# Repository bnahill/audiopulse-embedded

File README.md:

Android HiFi DPOAE Audio Interface
===================

This is part of the [Sana AudioPulse project](http://sana.mit.edu/audiopulse/) and may someday be officially moved over there.

The basic objective is an audio interface for an Android phone to output high-fidelity audio (two channels) to an earpiece and to record back audio from a microphone in the earpiece. As the features-of-interest in the response are below 0dB SPL, this requires very high precision.

Licensing
===================
This is an open-source project. Except where otherwise stated, this work is copyright 2014, Ben Nahill, free to be used, modified, and redistributed in accordance with terms of the GPLv3 license. Note that initially it was provided under a BSD-3 license.

Components
===================

*Updated to refer to rev2*

Control
-------------------
The main controller onboard is a Freescale Kinetis K20 ARM Cortex-M4 microcontroller. It has a 72MHz DSC core (running at 48MHz), a USB OTG interface with full-speed PHY, a full-duplex I2S interface to communicate with the CODEC, I2C to communicate with the headphone amplifier.

The USB interface is capable of up to 12Mb/s, which should support full-duplex 24-bit audio at 48kHz, which should require ~4.4Mb/s plus some inefficiency. That's fine but Android doesn't yet support USB audio input so processing is done onboard. An efficient mixed-precision C++ DSP library is included to perform processing similiar to that described in James Hall's *Handbook of Otoacoustic Emissions*.

CODEC
-------------------
The CODEC (ADC+DAC) must be as precise as possible on a budget. I've chosen the Asahi Kasei AK4621 which has stereo 24-bit differential input and output at 5V and up to 192kHz. Practically, the sampling rate will be 96kHz. S/(N+D) is 102dB for input and 100dB for output, which beats just about everything else I can find. The data interface is roughly I2S and is compatible with the K20 SAI.

Microphone
-------------------
Because of the extremely low required noise floor, the lowest self noise is desired in a microphone. As affordable microphones go, the best seems to be the Primo EM172 electret condenser microphone (ECM) with a noise floor around 14dB. Hopefully this is low enough to measure the necessary features in an averaged spectrum. Unfortunately, I haven't been able to find anything better than this.

Audio In
-------------------
The microphone input is scaled (roughly) to use the full-scale range of the ADC for an ~85dB SPL sine wave. The input conditioning changed substantially from rev1 to eliminate some of the discrete components and reduce power consumption and cost. It consists of a high impedance buffer followed by cascading Sallen-Key Chebyshev low-pass filters and inversion to feed the differential ADC.

A second audio input (since it's a stereo CODEC) is intended for use with the Etymotic ER-10C which does not need the gain stage. The differential input is not fully utilized in this case, as one end is tied to a virtual ground. We can also use this extra input for more advanced tests once DPOAE and some trials are in the bag.

Audio Out
-------------------
The output from the AK4621 is passed to the TI TPA6130A2 headphone amplifier. It has differential input and 98dB S/(N+D) and I2C volume control. It's optimized for a 32R load. This is currently a Knowles SR-series driver. Because the DAC generates lots of high-frequency nonsense that seems to upsed the amplifier, 2nd-order Sallen-Key filters had to be added to the differential signals.

Power
-------------------
Power became a bigger thing after realizing USB power is worse than expected (but that we really want to use it) in rev1. This is now dealt with by using a multi-level supply, boosting the USB input to ~6.5V before using a high-PSRR LDO to get a clean 5V. Digital stuff still runs off the USB supply and we get the ability to completely shut down power-hungry amplifiers and the CODEC when not in use.

Design
===================
The design so far consists of a PCB for the above electronics. The design (as of rev2b) is designed around OSH Park's 6/6 2-layer process, though it is also compatible with many other cheap services.

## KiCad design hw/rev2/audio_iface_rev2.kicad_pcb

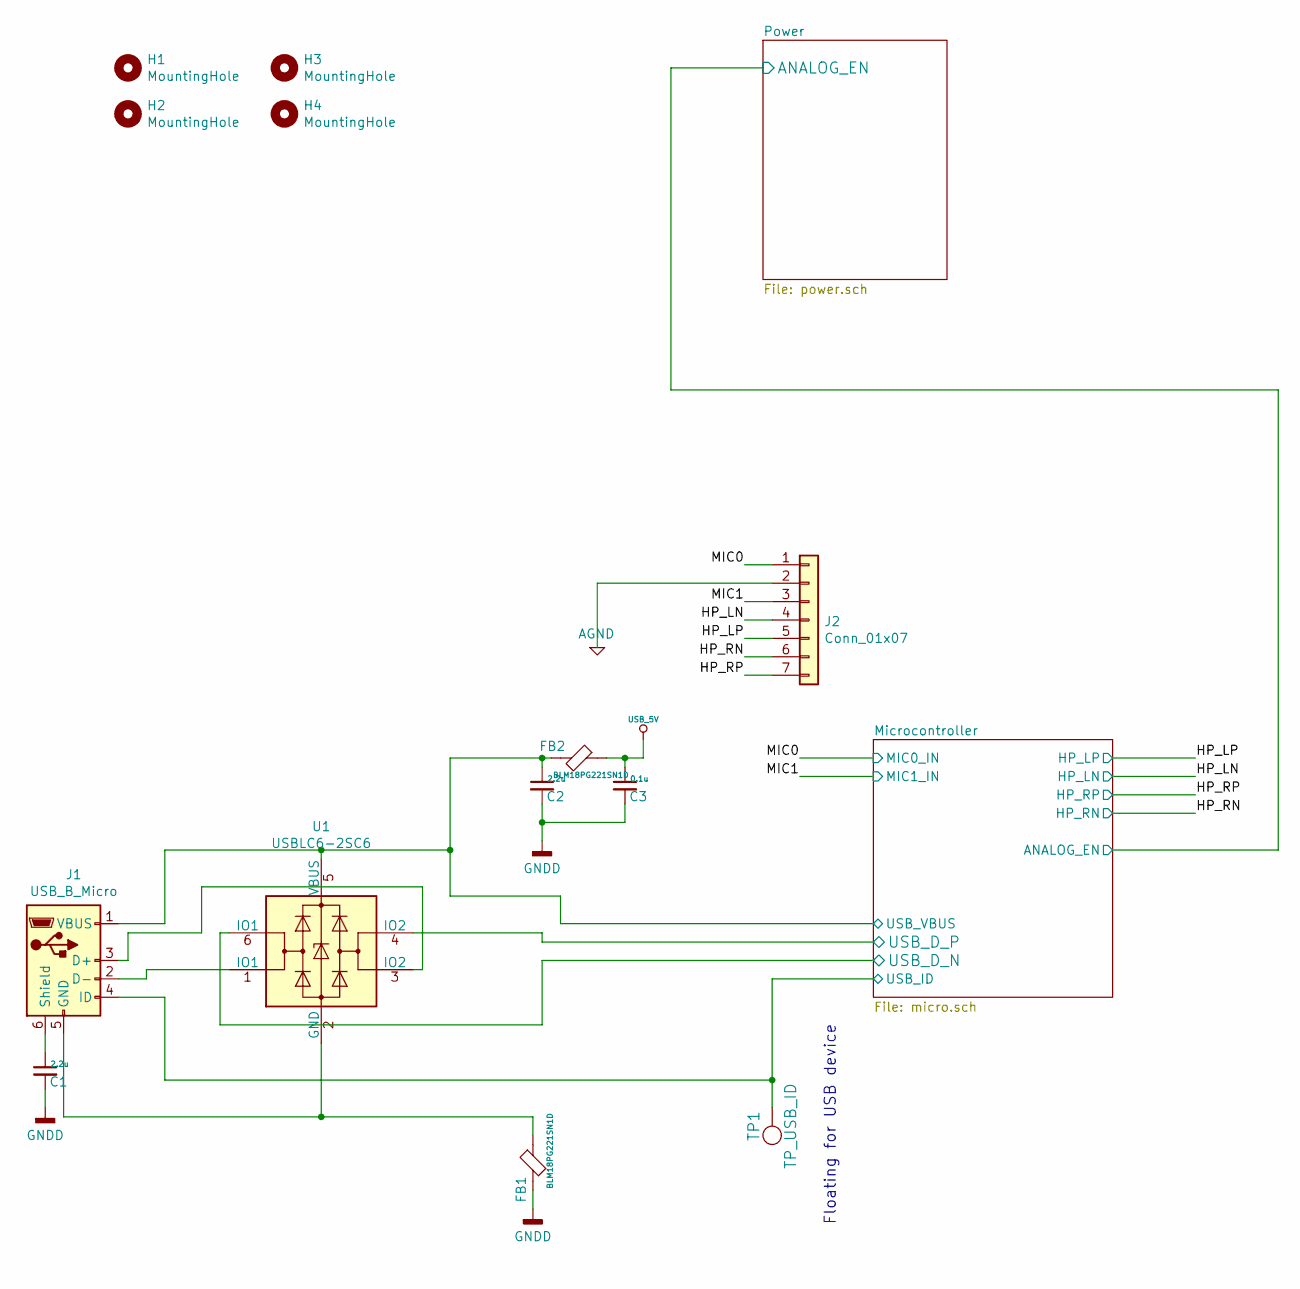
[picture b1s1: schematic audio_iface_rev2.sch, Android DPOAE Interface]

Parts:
C1, C2: 2.2u; C_0603_1608Metric_Pad1.05x0.95mm_HandSolder
C3: 0.1u; C_0402_1005Metric
FB1, FB2: BLM18PG221SN1D; L_0805_2012Metric_Pad1.15x1.40mm_HandSolder
H1, H2, H3, H4: MountingHole; MountingHole_2.2mm_M2
J1: USB_B_Micro; USB_Micro-B_Molex-105017-0001
J2: Conn_01x07; JST_PH_S7B-PH-K_1x07_P2.00mm_Horizontal
TP1: TP_USB_ID; SolderWirePad_single_1mmDrill
U1: USBLC6-2SC6; SOT-23-6

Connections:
/HP_LN: J2.4; also elsewhere on the board
/HP_LP: J2.5; also elsewhere on the board
/HP_RN: J2.6; also elsewhere on the board
/HP_RP: J2.7; also elsewhere on the board
/MIC0: J2.1; also elsewhere on the board
/MIC1: J2.3; also elsewhere on the board
/Microcontroller/USB_D_N: U1.6 (IO1); also elsewhere on the board
/Microcontroller/USB_D_P: U1.4 (IO2); also elsewhere on the board
/Microcontroller/USB_ID: J1.4 (ID), TP1.1; also elsewhere on the board
/Microcontroller/USB_VBUS: C2.1, FB2.2, J1.1 (VBUS), U1.5 (VBUS); also elsewhere on the board
unnamed: C1.1, J1.6 (Shield)
unnamed: FB1.1, J1.5 (GND), U1.2 (GND)
unnamed: J1.2 (D-), U1.1 (IO1)
unnamed: J1.3 (D+), U1.3 (IO2)
USB_5V: C3.1, FB2.1; also elsewhere on the board

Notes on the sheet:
Floating for USB device

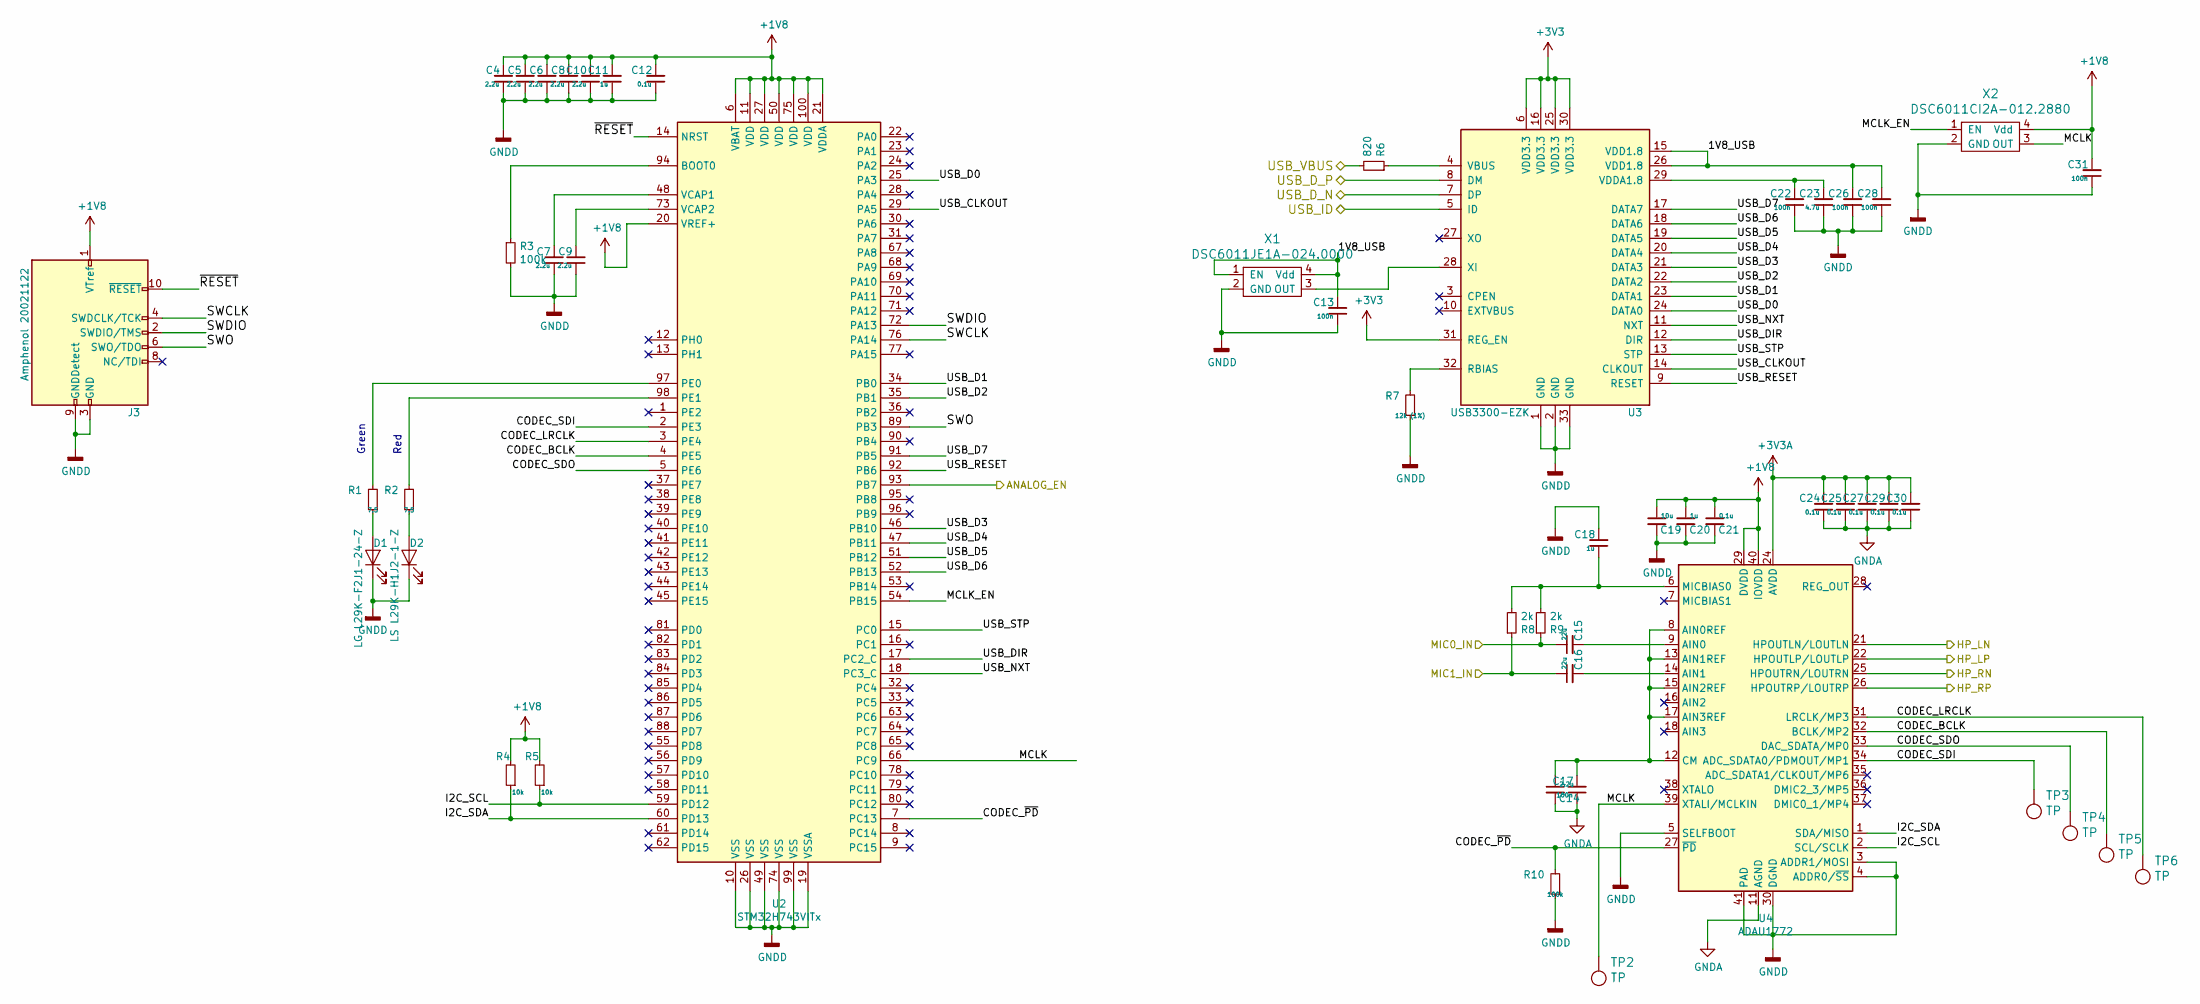
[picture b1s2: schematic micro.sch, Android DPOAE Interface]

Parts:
C4, C5, C6, C7, C8, C9, C10, C14: 2.2u; C_0603_1608Metric_Pad1.05x0.95mm_HandSolder
C11, C18, C20: 1u; C_0402_1005Metric
C12, C21, C24, C25, C27, C29, C30: 0.1u; C_0402_1005Metric
C13, C17, C22, C26, C28, C31: 100n; C_0402_1005Metric
C15, C16: 22u; C_1210_3225Metric
C19: 10u; C_0805_2012Metric_Pad1.15x1.40mm_HandSolder
C23: 4.7u; C_0805_2012Metric_Pad1.15x1.40mm_HandSolder
D1: LG L29K-F2J1-24-Z; LED_0603_1608Metric_Pad1.05x0.95mm_HandSolder
D2: LS L29K-H1J2-1-Z; LED_0603_1608Metric_Pad1.05x0.95mm_HandSolder
J3: Amphenol 20021122; PinHeader_2x05_P1.27mm_Vertical
R1, R2: 7.5; R_0402_1005Metric
R3, R10: 100k; R_0402_1005Metric
R4, R5: 10k; R_0402_1005Metric
R6: 820; R_0402_1005Metric
R7: 12k (1%); R_0402_1005Metric
R8, R9: 2k; R_0402_1005Metric
TP2, TP3, TP4, TP5, TP6: TP; SolderWirePad_single_1mmDrill
U2: STM32H743VITx; LQFP-100_14x14mm_P0.5mm
U3: USB3300-EZK; QFN-32-1EP_5x5mm_P0.5mm_EP3.1x3.1mm_ThermalVias
U4: ADAU1772; QFN-40-1EP_6x6mm_P0.5mm_EP4.6x4.6mm_ThermalVias
X1: DSC6011JE1A-024.0000; Oscillator_SMD_SeikoEpson_SG210-4Pin_2.5x2.0mm_HandSoldering
X2: DSC6011CI2A-012.2880; Oscillator_SMD_EuroQuartz_XO32-4Pin_3.2x2.5mm_HandSoldering

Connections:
+1V8: C4.2, C5.2, C6.2, C8.2, C10.2, C11.2, C12.2, C19.1, C20.1, C21.1, C31.2, J3.1 (VTref), R4.2, R5.2, U2.6 (VBAT), U2.11 (VDD), U2.20 (VREF+), U2.21 (VDDA), U2.27 (VDD), U2.50 (VDD), U2.75 (VDD), U2.100 (VDD), U4.29 (DVDD), U4.40 (IOVDD), X2.4 (Vdd); also elsewhere on the board
+3V3: U3.6 (VDD3.3), U3.16 (VDD3.3), U3.25 (VDD3.3), U3.30 (VDD3.3), U3.31 (REG_EN); also elsewhere on the board
+3V3A: C24.2, C25.2, C27.2, C29.2, C30.2, U4.10 (AVDD), U4.19 (AVDD), U4.24 (AVDD); also elsewhere on the board
/HP_LN: U4.21 (HPOUTLN/LOUTLN); also elsewhere on the board
/HP_LP: U4.22 (HPOUTLP/LOUTLP); also elsewhere on the board
/HP_RN: U4.25 (HPOUTRN/LOUTRN); also elsewhere on the board
/HP_RP: U4.26 (HPOUTRP/LOUTRP); also elsewhere on the board
/MIC0: C15.1, R9.1; also elsewhere on the board
/MIC1: C16.1, R8.1; also elsewhere on the board
/Microcontroller/1V8_USB: C13.2, C26.2, C28.2, U3.15 (VDD1.8), U3.26 (VDD1.8), X1.1 (EN), X1.4 (Vdd)
/Microcontroller/ANALOG_EN: U2.93 (PB7); also elsewhere on the board
/Microcontroller/CODEC_BCLK: TP5.1, U2.4 (PE5), U4.32 (BCLK/MP2)
/Microcontroller/CODEC_LRCLK: TP6.1, U2.3 (PE4), U4.31 (LRCLK/MP3)
/Microcontroller/CODEC_SDI: TP3.1, U2.2 (PE3), U4.34 (ADC_SDATA0/PDMOUT/MP1)
/Microcontroller/CODEC_SDO: TP4.1, U2.5 (PE6), U4.33 (DAC_SDATA/MP0)
/Microcontroller/CODEC_~PD: R10.2, U2.7 (PC13), U4.27 (~PD)
/Microcontroller/I2C_SCL: R5.1, U2.59 (PD12), U4.2 (SCL/SCLK)
/Microcontroller/I2C_SDA: R4.1, U2.60 (PD13), U4.1 (SDA/MISO)
/Microcontroller/MCLK: TP2.1, U2.66 (PC9), U4.39 (XTALI/MCLKIN), X2.3 (OUT)
/Microcontroller/MCLK_EN: U2.54 (PB15), X2.1 (EN)
/Microcontroller/SWCLK: J3.4 (SWDCLK/TCK), U2.76 (PA14)
/Microcontroller/SWDIO: J3.2 (SWDIO/TMS), U2.72 (PA13)
/Microcontroller/SWO: J3.6 (SWO/TDO), U2.89 (PB3)
/Microcontroller/USB_CLKOUT: U2.29 (PA5), U3.14 (CLKOUT)
/Microcontroller/USB_D0: U2.25 (PA3), U3.24 (DATA0)
/Microcontroller/USB_D1: U2.34 (PB0), U3.23 (DATA1)
/Microcontroller/USB_D2: U2.35 (PB1), U3.22 (DATA2)
/Microcontroller/USB_D3: U2.46 (PB10), U3.21 (DATA3)
/Microcontroller/USB_D4: U2.47 (PB11), U3.20 (DATA4)
/Microcontroller/USB_D5: U2.51 (PB12), U3.19 (DATA5)
/Microcontroller/USB_D6: U2.52 (PB13), U3.18 (DATA6)
/Microcontroller/USB_D7: U2.91 (PB5), U3.17 (DATA7)
/Microcontroller/USB_DIR: U2.17 (PC2_C), U3.12 (DIR)
/Microcontroller/USB_D_N: U3.7 (DP); also elsewhere on the board
/Microcontroller/USB_D_P: U3.8 (DM); also elsewhere on the board
/Microcontroller/USB_ID: U3.5 (ID); also elsewhere on the board
/Microcontroller/USB_NXT: U2.18 (PC3_C), U3.11 (NXT)
/Microcontroller/USB_RESET: U2.92 (PB6), U3.9 (RESET)
/Microcontroller/USB_STP: U2.15 (PC0), U3.13 (STP)
/Microcontroller/USB_VBUS: R6.2; also elsewhere on the board
/Microcontroller/~RESET: J3.10 (~RESET~), U2.14 (NRST)
unnamed: C7.2, U2.48 (VCAP1)
unnamed: C9.2, U2.73 (VCAP2)
unnamed: C14.1, C17.2, U4.8 (AIN0REF), U4.12 (CM), U4.13 (AIN1REF), U4.15 (AIN2REF), U4.17 (AIN3REF)
unnamed: C15.2, U4.9 (AIN0)
unnamed: C16.2, U4.14 (AIN1)
unnamed: C18.1, R8.2, R9.2, U4.6 (MICBIAS0)
unnamed: C22.2, C23.2, U3.29 (VDDA1.8)
unnamed: D1.2 (A), R1.1
unnamed: D2.2 (A), R2.1
unnamed: R1.2, U2.97 (PE0)
unnamed: R2.2, U2.98 (PE1)
unnamed: R3.1, U2.94 (BOOT0)
unnamed: R6.1, U3.4 (VBUS)
unnamed: R7.2, U3.32 (RBIAS)
unnamed: U3.28 (XI), X1.3 (OUT)

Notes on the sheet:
Green
Red

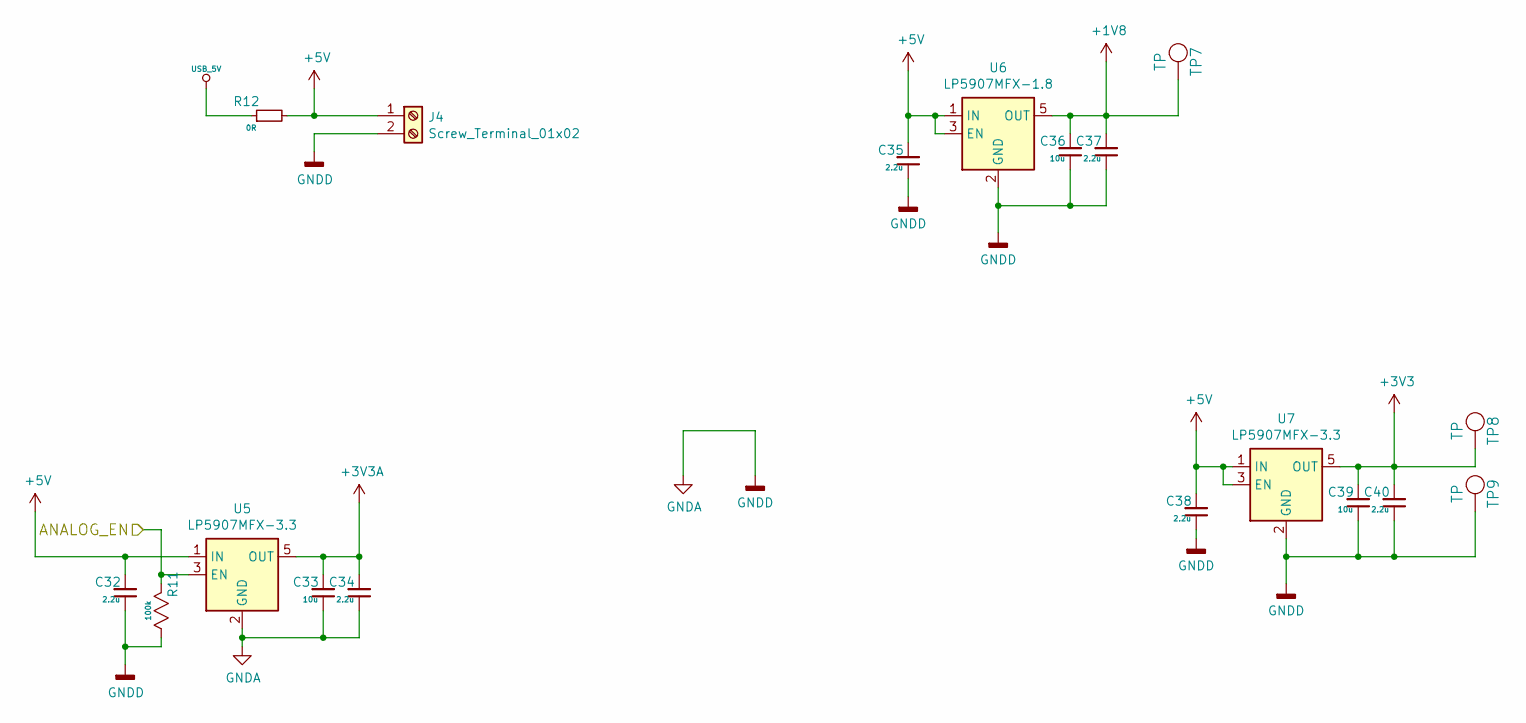
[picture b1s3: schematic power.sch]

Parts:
C32, C34, C35, C37, C38, C40: 2.2u; C_0603_1608Metric_Pad1.05x0.95mm_HandSolder
C33, C36, C39: 10u; C_0805_2012Metric_Pad1.15x1.40mm_HandSolder
J4: Screw_Terminal_01x02; PinHeader_1x02_P2.54mm_Vertical
R11: 100k; R_0402_1005Metric
R12: 0R; R_0402_1005Metric
TP7, TP8, TP9: TP; SolderWirePad_single_1mmDrill
U5, U7: LP5907MFX-3.3; SOT-23-5
U6: LP5907MFX-1.8; SOT-23-5

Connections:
+1V8: C36.2, C37.2, TP7.1, U6.5 (OUT); also elsewhere on the board
+3V3: C39.2, C40.2, TP8.1, U7.5 (OUT); also elsewhere on the board
+3V3A: C33.2, C34.2, U5.5 (OUT); also elsewhere on the board
+5V: C32.2, C35.2, C38.2, J4.1, R12.2, U5.1 (IN), U6.1 (IN), U6.3 (EN), U7.1 (IN), U7.3 (EN)
/Microcontroller/ANALOG_EN: R11.2, U5.3 (EN); also elsewhere on the board
USB_5V: R12.1; also elsewhere on the board

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
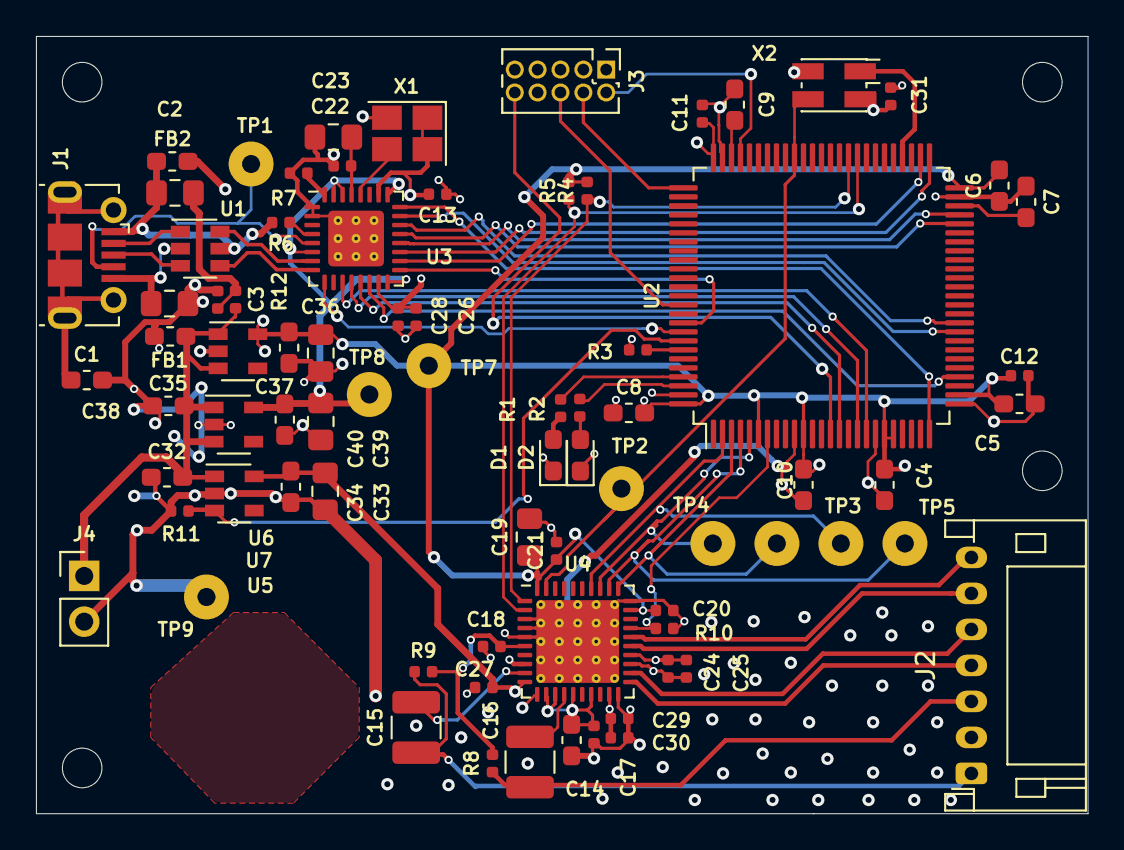
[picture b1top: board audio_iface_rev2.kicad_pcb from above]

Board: 4 copper layers, 58.4 x 43.2 mm, 82 parts (0 on the bottom side), 63 nets.

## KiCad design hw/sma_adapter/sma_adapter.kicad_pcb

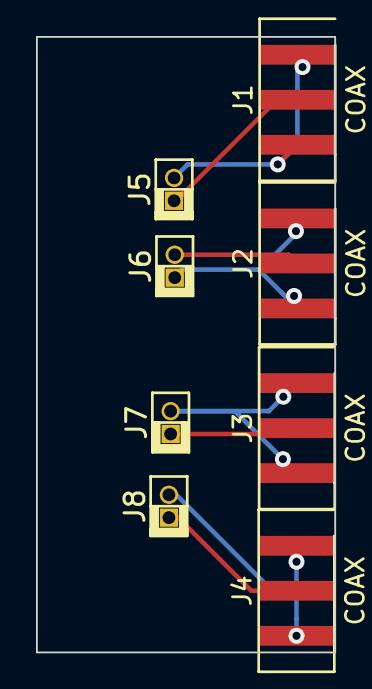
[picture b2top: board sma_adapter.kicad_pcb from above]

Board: 2 copper layers, 16.6 x 34.2 mm, 8 parts (0 on the bottom side), 8 nets.

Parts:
J1, J2, J3, J4: COAX; SMA_EDGE
J5, J6, J7, J8: CONN_2; HDR_2X1_50MIL

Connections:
unnamed: J2.2, J6.1
unnamed: J3.1, J7.1
unnamed: J3.2, J7.2
unnamed: J4.1, J8.1
unnamed: J4.2, J8.2
unnamed: J1.2, J5.2
unnamed: J2.1, J6.2
unnamed: J1.1, J5.1

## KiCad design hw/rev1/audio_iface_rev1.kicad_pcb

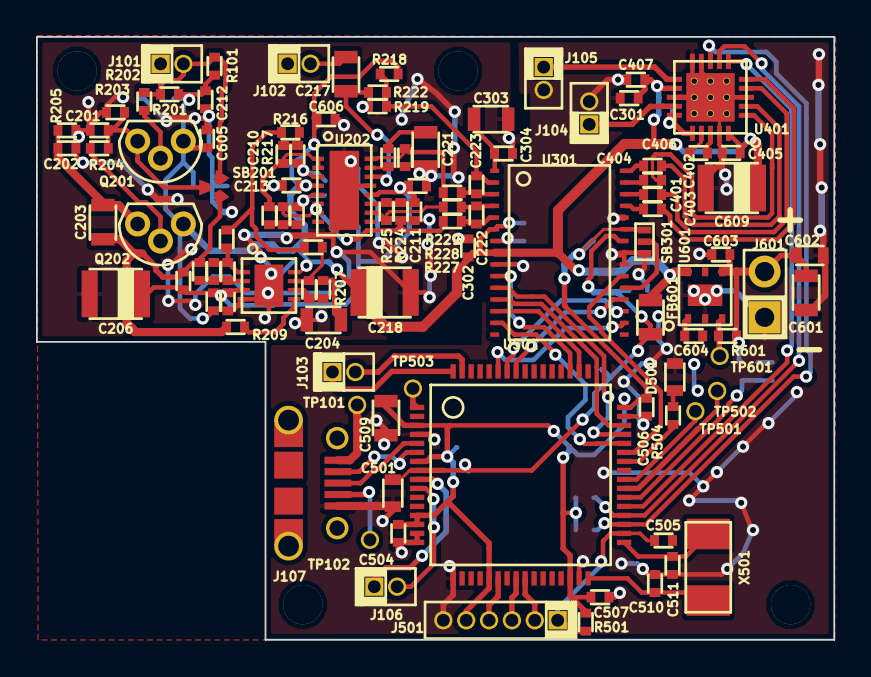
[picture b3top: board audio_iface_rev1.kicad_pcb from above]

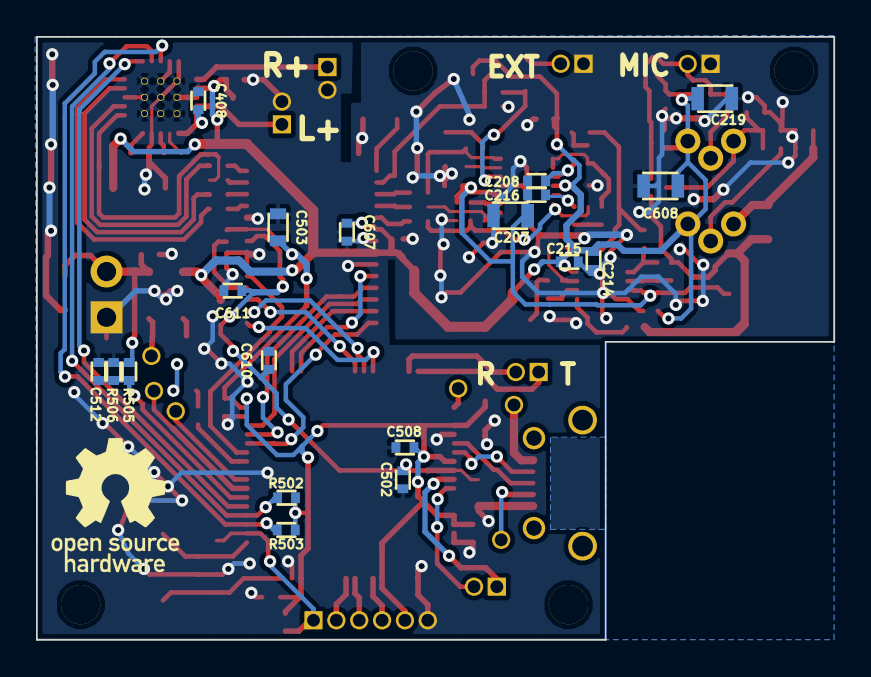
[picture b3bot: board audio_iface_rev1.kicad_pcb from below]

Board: 2 copper layers, 44.3 x 33.5 mm, 128 parts (20 on the bottom side), 85 nets.

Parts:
C201, C208, C216: 1n; SMD0402
C202, C401, C402, C403, C404: 0.47u; SMD0402
C203, C207: 10u 4V; SMD0805
C204, C217, C219, C221, C608: 10u 6.3V; SMD0805
C205, C210: 2n; SMD0402
C206: 100u 4V; SMD1411_POL
C209, C301, C405, C406, C407, C408, C504, C506, C512: 1u; SMD0402
C211, C302, C304, C502, C505, C507, C508: 0.1u; SMD0402
C212, C213, C606, C607, C610, C611: 0.1u 6.3V; SMD0402
C214, C215: 1u 6.3V; SMD0402
C218, C609: 100u 6.3V; SMD1411_POL
C220: 33n; SMD0402
C222, C223: 10n; SMD0402
C303: 10u; SMD0805
C501, C503: 2.2u; SMD0603
C509: 10n; SMD0805
C510, C511: CAP; SMD0402
C601: 10u 16V; SMD0805
C602: 2.2u 16V; SMD0603
C603, C604: 10n 16V; SMD0402
C605: 10n 6.3V; SMD0402
D501: LED; SMD0603
FB601: FB; SMD0805
J101, J102, J103, J104, J105, J106: CONN_2; HDR_2X1_50MIL
J107: USBMICROCONN; FCI_10118194
J501: CONN_6; HDR_6X1_50MIL
J601: CONN_2; HDR_2X1_100MIL
Q201, Q202: BC550; TO92-STRAIGHT-CBE
R101: 3.9k (1%); SMD0402
R201: 3.9k; SMD0402
R202, R204, R209, R213: 0R; SMD0402
R203: 5k; SMD0402
R205: 200; SMD0402
R206, R222: 250k; SMD0402
R207: 100 (1%); SMD0402
R208: 90 (1%); SMD0402
R210, R211: 5k (1%); SMD0402
R212, R504: RES; SMD0402
R214, R215: 1k (1%); SMD0402
R216: 8.87k (1%); SMD0402
R217: 26.1k (1%); SMD0402
R218, R219: 1k; SMD0402
R220: 1.4k (1%); SMD0402
R221: 4.53k (1%); SMD0402
R223, R226: 220 (1%); SMD0402
R224, R225: 10k (1%); SMD0402
R227, R228, R229: 22; SMD0402
R501, R502, R503: 10k; SMD0402
R505: 330k; SMD0402
R506: 100k; SMD0402
R601: 22k; SMD0402
SB201: SB_3
SB301: SB_2-1
SCREW_HOLE_2-56, SCREW_HOLE_2-56#2, SCREW_HOLE_2-56#3, SCREW_HOLE_2-56#4: VAL**; SCREW_HOLE_2-56
TP101: TP_VUSB; TP_HOLE
TP102: TP_USB_ID; TP_HOLE
TP501: TP_PTB3; TP_HOLE
TP502: TP_PTB16; TP_HOLE
TP503: TP_PTE0; TP_HOLE
TP601: TP_5VEN; TP_HOLE
U201: LT6201; LT_DFN8_DUAL
U202: LTC6242; LT_DFN16_QUAD
U301: AK4621; AK4621_VSOP30
U401: TPA6130A2RTJR; TPA8130A2-QFN20
U501: K20X7_QFP64; FREESCALE_QFP64
U601: LP2992AILD-5.0; TI_WSON6
VAL: OSHW
X501: XTAL; TXC_7A

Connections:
+3V: C503.2, C504.2, C506.2, C507.2, C508.2, C509.2, J501.5, R501.2, R502.2, R503.2, SB301.2, U301.25, U501.3, U501.7, U501.13, U501.14, U501.21, U501.30, U501.48
+5V: C501.2, C502.2, C610.1, C611.1, FB601.2, U301.24, U501.8
+5VA: C212.1, C213.1, C214.1, C215.1, C218.1, C219.1, C301.2, C302.2, C405.2, C407.2, C605.1, C606.1, C607.1, C608.1, C609.1, FB601.1, Q201.C, Q202.C, R101.2, R201.2, R214.2, R218.2, U201.Vdd, U202.Vdd, U301.6, U301.8, U401.12, U401.20, U601.6
/Audio In/EXT_IN: C217.1, J102.2
/Audio In/MIC_IN: J101.2, R101.1, R201.1, R202.1, SB201.2
/CODEC/AINL+: C222.1, R228.2, U301.4
/CODEC/AINL-: C222.2, R227.2, U301.5
/CODEC/AINR+: C223.1, R218.1, R219.2, R222.1, U301.2
/CODEC/AINR-: C223.2, R229.2, U301.3
/CODEC/AOUTL+: C401.1, U301.28
/CODEC/AOUTL-: C403.1, U301.27
/CODEC/AOUTR+: C404.1, U301.30
/CODEC/AOUTR-: C402.1, U301.29
/CODEC/BICK: U301.12, U501.46
/HP Amp/HPL: J104.1, U401.14
/HP Amp/HPR: J105.1, U401.11
/Microcontroller/CODEC_LRCK: U301.11, U501.45
/Microcontroller/CODEC_MCLK: U301.10, U501.51
/Microcontroller/CODEC_PDN: U301.21, U501.43
/Microcontroller/CODEC_SDIN: U301.13, U501.50
/Microcontroller/CODEC_SDO: U301.14, U501.44
/Microcontroller/HP_~SD: U401.6, U501.37
/Microcontroller/I2C0_SCL: R503.1, U401.8, U501.35
/Microcontroller/I2C0_SDA: R502.1, U401.7, U501.36
/Microcontroller/PGA0_D+: J106.1, U501.9
/Microcontroller/PGA0_D-: J106.2, U501.10
/Microcontroller/RESET: C505.1, J501.1, R501.1, U501.34
/Microcontroller/SPI1_CS_CODEC: U301.19, U501.57
/Microcontroller/SPI1_SCK: U301.18, U501.58
/Microcontroller/SPI1_SOUT: U301.17, U501.59
/Microcontroller/SWCLK: J501.4, U501.22
/Microcontroller/SWDIO: J501.2, U501.25
/Microcontroller/SWO: J501.3, U501.24
/Microcontroller/UART0_RX: J103.2, U501.63
/Microcontroller/UART0_TX: J103.1, U501.64
/Microcontroller/USB_D+: J107.3, U501.5
/Microcontroller/USB_D-: J107.2, U501.6
AGND_IN: C201.1, C202.1, C204.2, C206.2, C207.2, C209.2, C211.2, C212.2, C213.2, C214.2, C215.2, C218.2, C219.2, C221.2, C301.1, C302.1, C303.1, C304.1, C405.1, C407.1, C408.1, C501.1, C502.1, C503.1, C504.1, C505.2, C506.1, C507.1, C508.1, C509.1, C510.2, C511.2, C512.1, C601.1, C602.1, C603.1, C604.1, C605.2, C606.2, C607.2, C608.2, C609.2, C610.2, C611.2, D501.2, J101.1, J102.1, J104.2, J105.2, J107.5, J501.6, J601.1, R203.1, R205.1, R215.1, R219.1, R506.1, SB301.3, U201.Vss, U202.Vss, U301.7, U301.9, U301.22, U301.23, U301.26, U401.3, U401.9, U401.10, U401.13, U401.19, U401.PAD, U501.4, U501.15, U501.16, U501.17, U501.31, U501.47, U601.2, U601.PAD
unnamed: J107.1, TP101.1
unnamed: J107.4, TP102.1
unnamed: R224.2, R225.1, U202.n3
unnamed: R225.2, R228.1, U202.o3
unnamed: C216.2, R221.2, U202.p2
unnamed: C208.2, R217.2, U202.p1
unnamed: C220.1, R220.2, R221.1
unnamed: R209.2, U201.p2
unnamed: C204.1, R207.1
unnamed: Q202.B, R204.2
unnamed: Q201.B, R202.2
unnamed: R212.1, R213.2, R216.1
unnamed: R207.2, R210.1, U201.n2
unnamed: R210.2, R213.1, U201.o2
unnamed: C201.2, Q201.E, R203.2, R204.1, SB201.1
unnamed: C202.2, C203.1, Q202.E, R205.2
unnamed: C220.2, R224.1, R227.1, U202.n2, U202.o2
unnamed: C210.1, R216.2, R217.1
unnamed: C210.2, R220.1, U202.n1, U202.o1
unnamed: C203.2, R206.2, R208.1, R209.1, SB201.3
unnamed: R226.2, R229.1, U202.o4
unnamed: C217.2, R222.2, U202.p4
unnamed: C221.1, R223.1
unnamed: R223.2, R226.1, U202.n4
unnamed: C205.2, R211.2, R212.2, U201.o1
unnamed: C205.1, R208.2, R211.1, U201.n1
unnamed: C303.2, C304.2, U301.1
unnamed: SB301.1, U301.20
unnamed: C403.2, U401.5
unnamed: C406.1, U401.18
unnamed: C406.2, U401.17
unnamed: C404.2, U401.2
unnamed: C402.2, U401.1
unnamed: C401.2, U401.4
unnamed: C408.2, U401.15, U401.16
unnamed: TP502.1, U501.39
unnamed: TP503.1, U501.1
unnamed: TP501.1, U501.40
unnamed: R504.2, U501.42
unnamed: C512.2, R505.1, R506.2, U501.38
unnamed: C510.1, U501.32, X501.2
unnamed: C511.1, U501.33, X501.1
unnamed: D501.1, R504.1
unnamed: C604.2, U601.1
unnamed: R601.2, TP601.1, U601.3
VCC: C601.2, C602.2, C603.2, J601.2, R505.2, R601.1, U601.4
VCOM_VRT: C206.1, C207.1, C208.1, C209.1, C211.1, C216.1, R206.1, R214.1, R215.2, U201.p1, U202.p3

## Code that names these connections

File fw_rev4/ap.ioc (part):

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Mcu.Name=STM32H753VITx
Mcu.Package=LQFP100
Mcu.UserName=STM32H753VITx
PA13\ (JTMS/SWDIO).Mode=Trace_Asynchronous_SW
PA13\ (JTMS/SWDIO).Signal=DEBUG_JTMS-SWDIO
PA14\ (JTCK/SWCLK).Mode=Trace_Asynchronous_SW
PA14\ (JTCK/SWCLK).Signal=DEBUG_JTCK-SWCLK
PA3.Mode=Device_HS
PA3.Signal=USB_OTG_HS_ULPI_D0
PA4.Mode=Activate_SOF_FS
PA4.Signal=USB_OTG_HS_SOF
PA5.Mode=Device_HS
PA5.Signal=USB_OTG_HS_ULPI_CK
PB0.Mode=Device_HS
PB0.Signal=USB_OTG_HS_ULPI_D1
PB1.Mode=Device_HS
PB1.Signal=USB_OTG_HS_ULPI_D2
PB10.Mode=Device_HS
PB10.Signal=USB_OTG_HS_ULPI_D3
PB11.Mode=Device_HS
PB11.Signal=USB_OTG_HS_ULPI_D4
PB12.Mode=Device_HS
PB12.Signal=USB_OTG_HS_ULPI_D5
PB13.Mode=Device_HS
PB13.Signal=USB_OTG_HS_ULPI_D6
PB15.Signal=GPIO_Output
PB3\ (JTDO/TRACESWO).Mode=Trace_Asynchronous_SW
PB3\ (JTDO/TRACESWO).Signal=DEBUG_JTDO-SWO
PB5.Mode=Device_HS
PB5.Signal=USB_OTG_HS_ULPI_D7
PB6.Signal=GPIO_Output
PB7.Signal=GPIO_Output
PC0.Mode=Device_HS
PC0.Signal=USB_OTG_HS_ULPI_STP
PC13.Signal=GPIO_Output
PC2_C.Mode=Device_HS
PC2_C.Signal=USB_OTG_HS_ULPI_DIR
PC3_C.Mode=Device_HS
PC3_C.Signal=USB_OTG_HS_ULPI_NXT
PC9.Mode=Audio_ClockIn
PC9.Signal=I2S_CKIN
PD12.Mode=I2C
PD12.Signal=I2C4_SCL
PD13.Mode=I2C
PD13.Signal=I2C4_SDA
PD8.Mode=Asynchronous
PD8.Signal=USART3_TX
PD9.Mode=Asynchronous
PD9.Signal=USART3_RX
PE0.Signal=GPIO_Output
PE1.Signal=GPIO_Output
PE3.Mode=SAI_B_SyncSlave
PE3.Signal=SAI1_SD_B
PE4.Mode=SAI_A_Master
PE4.Signal=SAI1_FS_A
PE5.Mode=SAI_A_Master
PE5.Signal=SAI1_SCK_A
PE6.Mode=SAI_A_Master
PE6.Signal=SAI1_SD_A
RCC.SYSCLKFreq_VALUE=480000000
RCC.SYSCLKSource=RCC_SYSCLKSOURCE_PLLCLK
board=custom

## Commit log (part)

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2013-09-11 Initial commit of almost nothing
2013-09-12 Preamp is better...
2013-09-13 Reduced noise on preamp, can reduce components further
2013-09-20 Amplifier design complete, trying to get it reviewed
2013-10-01 Added some datasheets
2013-10-03 Migrated to Kinetis K20, wired up controls for CODEC
2013-10-03 Started to specify components
2013-10-04 Made footprint for micro and amps
2013-10-04 Better supply isolation and added regulator
2013-10-04 Added docs for regulator and uC mechanical drawings
2013-10-06 Added footprints for just about everything else. Also added some comments to the schematic.
2013-10-07 Added some connector and solderbridge footprints
2013-10-07 Annotate components, associate footprints, and begin component placement
2013-10-08 Added a bunch of 3D models
2013-10-12 Completed PCB with new K20x72 instead.
2013-10-14 Added supply voltage ADC input to monitor battery levels
2013-10-19 Updated license and docs
2013-11-22 Start assmebling required software components
2013-11-22 Added startup file...
2013-11-24 Added SPI driver for codec, still not getting an I2S response
2013-11-29 Started switch to HID interface
2013-11-30 Fixed issue where chip would only boot with debugger I was writing wrong register address while disabling watchdog... Now USB starts on its own
2013-12-04 Changed interface configuration for codec. Might work better.
2013-12-04 At least SPI works right... CODEC still not outputting right
2013-12-17 CODEC responds correctly now
2013-12-18 Audio input and output both seem to work, but require more testing
2013-12-19 Start work on making HID interface work correctly
2013-12-19 Added small libusb test
2013-12-25 Started experimentation with HID w/o int out ep
2013-12-27 HID works with Android -- now to get some basic scheduling
2013-12-27 Started OAE testing control and added protothreads
2013-12-27 Restructured a bit and added audio capture logic
    By default, audio capture now requires channels to be individually enabled
    Also, a protothread does decimation, still untested...
2013-12-29 Added math and timer libraries and tone generator
2013-12-30 Added driver for TPA6130A2
2013-12-31 Output works
2014-01-03 Changed controller around a bit to use different state config
2014-01-03 Improved a lot of the math function Now more correct and robust Also power outputs are now in Q1.30 for safety
2014-01-03 More math fixes, more controller
2014-01-04 Added test code for Android
2014-01-04 Added command interface class to Android test app
2014-01-04 Quick test for linker
2014-01-05 Force vertical orientation for Android
2014-01-05 Fixed blatant hard fault in power averaging function
2014-01-07 Some changes to controller logic to make more clear states
2014-01-09 Added some GDB support with PyCortexMDebug
2014-01-09 Huge controller updates: Moved to more explicit state machine implementation Added control for switching HP amp as needed Timer is still broken
2014-01-09 Minor neatness things, added more flexible clock config stuff
2014-01-09 Made text boxes in Android monospace. It looks better for this.
2014-01-09 Made it so that subsystems transition to DONE state Also LED indicates running test
2014-01-10 Test works somewhat: Tone generation and timing is great Test starts and finishes correctly and can perform multiple tests in sequence. DSP seems okay but there is definitely some error in there. I t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
2014-01-11 Fixed transform output problems which cause negative power The problem was that the constants 1/n and 1-1/n were being generated incorrectly; fixed sFractional::mk_frac
2014-01-11 Made output of PSD double for android. Also can display PSD
2014-01-11 Transform output format and order fixed and able to send data to android
2014-01-11 Fixed mistakenly adjusting size of wrong buffer in last commit
2014-01-19 Updated Android UI to have more options
2014-01-19 Changed default values and simplified android test interface
2014-01-19 Changed to linear interpolation for speaker calibration and... Also enable LED on start Also use larger integer component for PSD
2014-01-28 Added basic 16-band online calibration for input
2014-01-30 Started really simple PyUSB/PySide PC interace for AudioPulse
2014-01-30 Simple test of Python interface works. Now for a GUI
2014-02-01 Reset on USB enumeration
2014-02-01 PC GUI can now display and compare plots
2014-02-02 Added simulation for simplified preamp design
2014-02-02 Added calibration to Python UI
2014-02-02 Added legend and units to plots
2014-02-04 Small fixes to UI
2014-02-10 Tiny UI fixes for overlap and text
2014-02-11 Added more complete support throughout firmware for mixing channels
2014-02-14 Added support for channel mixing and saving waveforms to UI
2014-02-18 Firmware sample subtraction works. Now for stationary noise subtraction
2014-03-24 Scaling of PSDs should be cleaner and reduce SQNR
2014-04-04 Made startup actually run static constructors
2014-04-04 A lot of changes to add support for waveform dumping NOTE: Some constants were changed here and adjustments should be made
2014-04-16 Fixed FIR order initialized to arbitrary "5"
2014-04-17 Added datasheet for TPA152 class AB headphone amplifier
2014-04-22 Started rev2a design based on rev1a
2014-05-06 ACTUALLY ADDED THE PCB THIS TIME... A few more changes Added dimensions and some decorative silks Also got rid of reference silks for most passives and reorganized the rest. TODO: Add pads for that s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
2014-05-06 Added crystal documentation
2014-05-07 Updated simulation to match what's being manufactured
2014-05-08 rev2a finalized
2014-05-08 Added submitted gerbers for rev2a
2014-05-28 Updated firmware sources to match rev2a Power supply reset architecture now built into test coordination Analog domain components now have split initialization *All untested*
2014-06-17 Some real trivial changes
2014-06-23 Test coordination and input processing works with rev2a
2014-06-29 Rev 2a sent off for manufacturing: Slot added instead of drill hole at audio IO end Drill added near center Fixed huge error in HP amp schematic/layout Got rid of more labels Got rid of redundant UAR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
2014-07-26 Changed a lot of number formats for output
2014-07-26 Fixed so it will compile in 32k of RAM TODO: Figure out why switching to packaged GCC 4.9.1 increased RAM usage
2014-08-04 CMSIS upgraded to 4.0 -- #includes need to change for this
2014-08-04 GDB initialization now calls JLink, then initializes DWT
2014-08-04 Modify code to fit with mixed-precision lib better and support CMSIS 4 This should actually work
2014-08-15 Firmware: Fixed buffer iterator problem that was causing massive distortion UI: More reliable waveform dumps
2014-08-30 Modified UI to be aware of PSD fractional format
2014-08-30 Added filter design script for shift to IIR cascade Requires scipy, numpy, and matplotlib(for plots)
2014-08-30 Fixed some things with the filter designer: Fixed bug in quantization Added plotting of quantized frequency response Added different infinity and first-only gain distributions TODO!: Actual rounding 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
2014-08-31 Filter design got a bit more stuff: Rounding instead of truncation Quantized plot uses sections (correct transfer function!)
2014-08-31 Cosmetic improvements to filter designer
2014-09-10 Added options to switch between IIR and FIR (because IIR is broken now)
2014-09-23 Minimal framework for bounds checking added Nothing done with it
2014-10-03 Minor change to abstract power control at Platform level
2014-10-17 Added values for LED resistors
2014-11-25 matlab simulation script
2014-11-27 fixed issues with simulation
2014-11-28 "added option to generate stimulus frequency at an approximate frequency from the original that will minimize FFT leakage due to sample size"
2014-11-28 added decimation stage to the analysis
2014-11-29 Fixed bug in accumulating waveforms to allow for overlap (loopback)
2014-11-29 Added rectangular window option
2014-11-29 Added wavetable sine implementation for matlab
2014-12-20 Added K22F512 files
2014-12-20 Added fsl_device_registers.h
2014-12-20 Added documentation for K22
2014-12-22 Added fixes again to at least enumerate on USB and almost do tests
2015-01-04 Added plotting to GDB interface -- fix it
2015-01-04 Added float support to UI
2015-01-05 Fixed most of GDB plotting, didn't test plotting multiple symbols in actual GDB land
2015-01-05 Actually fixed plotting multiple symbols
2015-01-12 Fancier debug plotting, switched to external MCLK
2015-02-12 Added fancy adapter board to SMA connectors
2015-04-22 Fixed to run correctly with FPU
2015-05-12 Added serial flash module to schematic and began layout
2015-05-13 Forgot to add Micron BGA footprint
2015-06-01 Updated layout to what was submitted for rev3a
2015-06-09 Added a bunch of stuff to make flash work in SW
2015-06-09 Fixed some of it
2015-07-15 LOTS: Added Flash, converted SPI and codec away from static classes
2015-08-02 Fixed codec initialization to reliably preserve the same channel mapping
2015-10-08 Added SysTick handling for an easier-to-use timer
2015-10-21 Added small configuration bits to codec initialization. Nothing important.
2015-10-21 Moved wave generation to floating point with saturation
2015-11-03 Cleaned up tone generation that I thought I fixed last time--also sped up input sample conversion. Output now capped at 80dB
2015-11-28 After some modifications, I can send 64-byte isochronous messages
2015-11-28 Tried changing transfer size
2015-11-28 Small changes for testing
2015-11-29 Holy shark apparently it can send more samples!
    Also added a queue for to do sending off more samples
2015-11-29 Started reworking input processing chain
    This will allow for continuous audio input for USB
2015-11-29 Added option to add samples directly to queue without formatting
2015-12-21 Added a simulated input stream, fixed some bugs
2015-12-27 Solved problem of jumpy USB traffic. Buffering fixed now too
    This was tested only on the lappy toppy. Still to be tested elsewhere
2015-12-28 Modified python interface to use new HID endpoints
2015-12-28 Minor adjustments to USB composite junk
2016-01-01 Added HID report descriptor, lots of debugging to figure out why HID messages aren't going through
2016-03-04 Tried replacing HID with a CDC device
    Maybe Freescale sucks less at this...
2016-03-26 More complete CDC implementation
2016-04-01 Started using the UART driver, still debugging
2016-04-02 Made some really minor changes to UART driver
2016-09-20 Started board upgrade to 4 layers and better signal isolation
2016-09-30 Submitted PCB revision
2016-10-23 C++11 compatibility fix:
    More recent versions of gcc started enforcing constexpr restrictions
    for allowing reinterpret_cast to be constant. This makes it impossible
    to use peripheral addresses by pointer in constexpr initialization...
    The solution has been to add the references in the linker instead,
    making peripherals into actual objects.
    Results yet untested.
2016-10-30 Upgraded UI to QT5, added plot navigation and custom labels
2016-11-08 Accumulate in abs(transform) rather than power. Also...
    Output levels pushed to sane values (within 5dB of accurate)
2016-11-08 Change default stimulus levels
2016-11-09 Started wacky transition to Atmel's SAM S70N
    For, you know, more hootz
2016-11-10 Added 3V regulator, started wiring
2016-11-10 Added code for reading I2S and processing
2016-11-10 Frequency interpolation for wavegen
2016-11-13 Simplified input processing, reduced amp count by 2
2016-11-13 Finished simlified design
2016-11-16 Lots of layout and grounding changes. DRC good
2016-12-27 Fixed power connections for S70--submitted PCB
2017-01-01 Modified feedback values on PCB
2017-03-13 Fixed some mis-wiring to the USBHS PHY. It should work now...
2017-03-20 Finished schematic and layout with STM32F7
2017-03-29 Updated oscillator values
2017-05-28 Functioning USB on ChibiOS, now porting over drivers
2017-06-20 Filled out codec driver
2018-01-04 Update submodule reference
2019-01-28 Most of a schematic
2019-02-03 Schematic roughly complete
2019-09-17 Added teensy library, fixed footprint and lib paths
2019-09-17 Much more routing
2019-09-25 Design nearly complete. One more check.
2019-11-04 Added software for new board rev
2019-11-04 Made CMakeLists happier about building
